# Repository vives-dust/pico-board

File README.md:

# DUST Capacitive Moisture Pico board

| Front | Back |
|---|---|
|  |

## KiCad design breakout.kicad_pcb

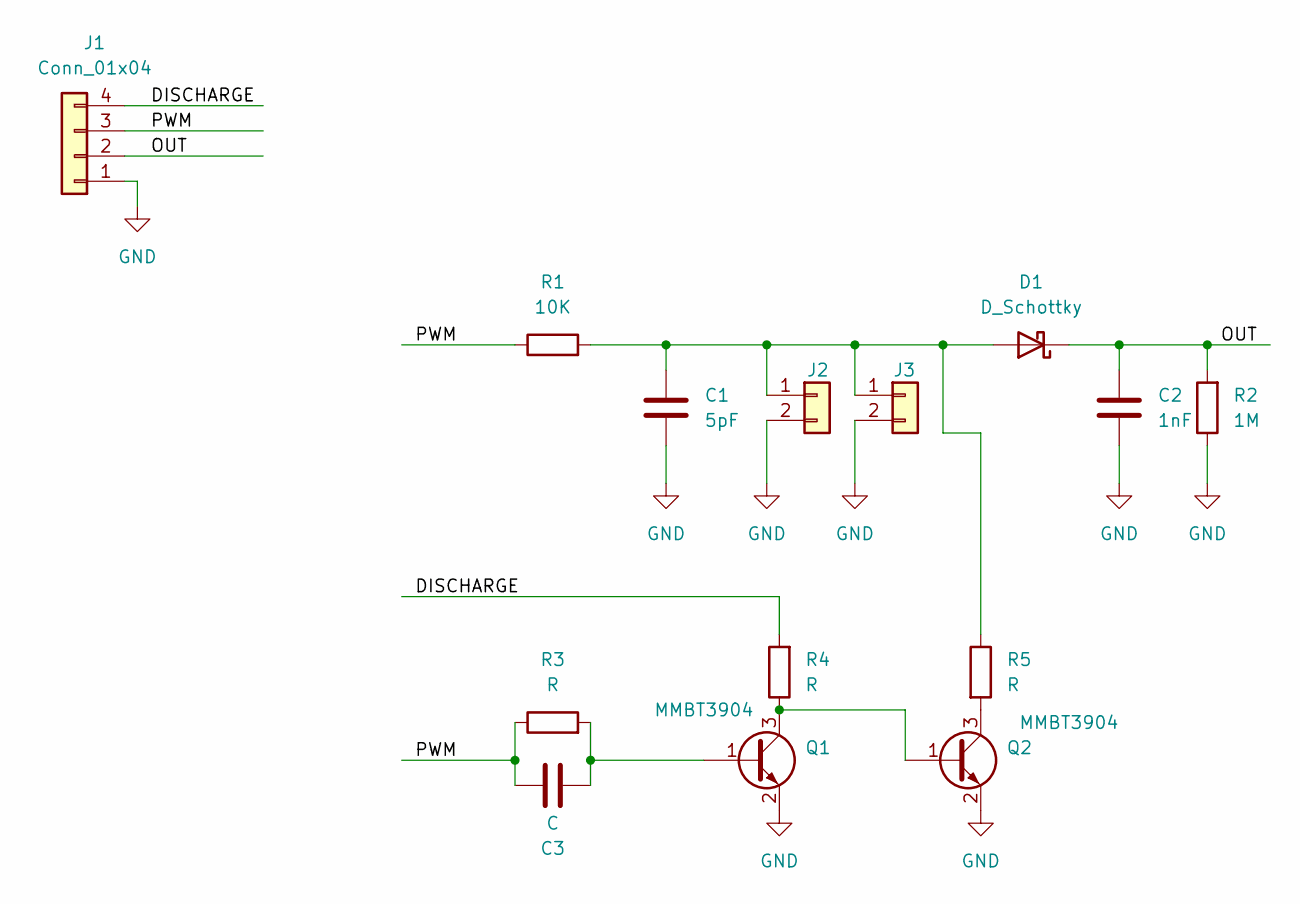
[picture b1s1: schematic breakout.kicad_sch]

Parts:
C1: 5pF; C_0603_1608Metric
C2: 1nF; C_0603_1608Metric
C3: C; C_0603_1608Metric
D1: D_Schottky; D_SOD-123
J1: Conn_01x04; PinHeader_1x04_P2.54mm_Vertical
J2: Conn_01x02; PTSM 0.5-2-HH-2.5-SMD
J3: Conn_01x02; PinHeader_1x02_P2.54mm_Vertical
Q1, Q2: MMBT3904; SOT-23
R1: 10K; R_0603_1608Metric
R2: 1M; R_0603_1608Metric
R3, R4, R5: R; R_0603_1608Metric

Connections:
/DISCHARGE: J1.4, R4.2
/OUT: C2.1, D1.1 (K), J1.2, R2.2
/PWM: C3.2, J1.3, R1.1, R3.1
GND: C1.2, C2.2, J1.1, J2.2, J3.2, Q1.2 (E), Q2.2 (E), R2.1
unnamed: C1.1, D1.2 (A), J2.1, J3.1, R1.2, R5.1
unnamed: C3.1, Q1.1 (B), R3.2
unnamed: Q1.3 (C), Q2.1 (B), R4.1
unnamed: Q2.3 (C), R5.2

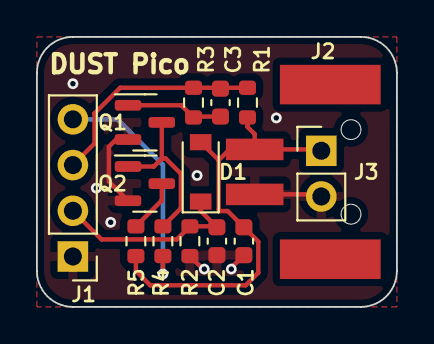
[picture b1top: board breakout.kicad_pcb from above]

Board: 2 copper layers, 20.0 x 15.0 mm, 14 parts (0 on the bottom side), 8 nets.

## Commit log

2021-09-06 initial prototype
2021-09-06 v1.0
2021-09-06 add rounded borders :)
2021-09-20 add discharge circuit
2021-12-29 Update generated images
2021-12-29 update pcb
2022-01-27 create panel
